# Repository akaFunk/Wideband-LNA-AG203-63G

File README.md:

# Wideband LNA AG203-63G
The Qorvo AG203-63G [1] is a cheap amplifier with (quite) low noise and very high bandwidth. The noise figure is roughly 3 dB, gain is around 20 dB and it works from DC to 6 GHz. It does not reuqire external matching, thus the schematic is very simple.

The PCB has a height of 0.6 mm, which is crucial (at least at higher frequencies) and it was ordered in China [2]. The populated PCB was soldered into a tinplate filter housing FG1 of size 37x20x20 mm [3]. To get the DC voltage into the housing a 1000 pF feed through capacitor DF 38 [4] was used.

The fully build amplifier has been characterized using an DG8SAQ VNA [5]. The input return loss is ca. 15 dB for 70 cm band (433 MHz) and ca. 21 dB for 2 m band (145 MHz). The data of the measurement can be found in the measurements folder. When you want to operate the LNA at a higher frequency, you should replace the coupling capacitors C1 and C3 and the feed inductor L1 with smaller values. See the datasheet [1] for details.

## Images

## References
[1] https://www.qorvo.com/products/p/AG203-63G  
[2] http://www.elecrow.com  
[3] http://www.schubert-gehaeuse.de/prod01.htm  
[4] http://www.oppermann-electronic.de/html/durchf__c_s.html  
[5] https://www.sdr-kits.net/introducing-DG8SAQ-VNWA3

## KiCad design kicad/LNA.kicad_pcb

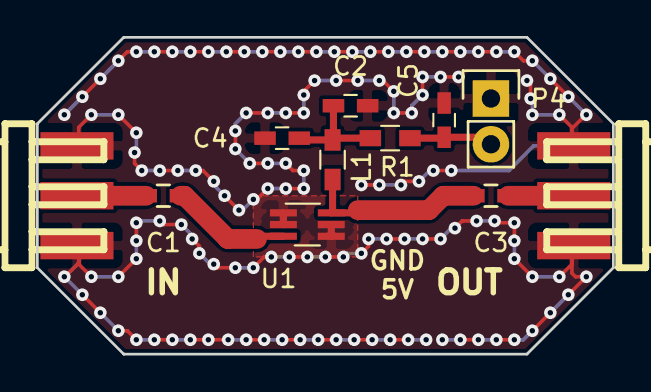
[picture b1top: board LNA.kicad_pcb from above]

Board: 2 copper layers, 32.0 x 17.6 mm, 11 parts (0 on the bottom side), 7 nets.

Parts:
C1, C2, C3, C4: 10n; C_0603_HandSoldering
C5: 100n; C_0603_HandSoldering
L1: 470n; L_0603_HandSoldering
P1: OUT; CON-SMA-EDGE
P3: IN; CON-SMA-EDGE
P4: VC1; Pin_Header_Straight_1x02
R1: 47.5; R_0603_HandSoldering
U1: AG203-63G; SOT-363_SC-70-6_Handsoldering

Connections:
GND: C2.2, C4.2, C5.2, P1.2, P3.2, P4.1, U1.1, U1.2, U1.4, U1.5
unnamed: C1.1, U1.3
unnamed: C1.2, P3.1
unnamed: C2.1, C4.1, L1.1, R1.2
unnamed: C3.1, P1.1
unnamed: C3.2, L1.2, U1.6
VCC: C5.1, P4.2, R1.1

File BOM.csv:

Reference,Quantity,Value,MPN
P1,1,RF1,2579819
P3,1,RF2,2579819
C1;C3;C4;C2,4,10n,C0603X103J3JACAUTO
C5,1,100n,C0603X104J3RACTU
P4,1,VC1,
U1,1,AG203-63G,AG203-63G
L1,1,470n,L-14WR47JV4E
R1,1,47,

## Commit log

2018-05-19 Added license
2018-05-19 corrected DG8SAQ link in references
2018-05-19 Fixed typo: though -> through
